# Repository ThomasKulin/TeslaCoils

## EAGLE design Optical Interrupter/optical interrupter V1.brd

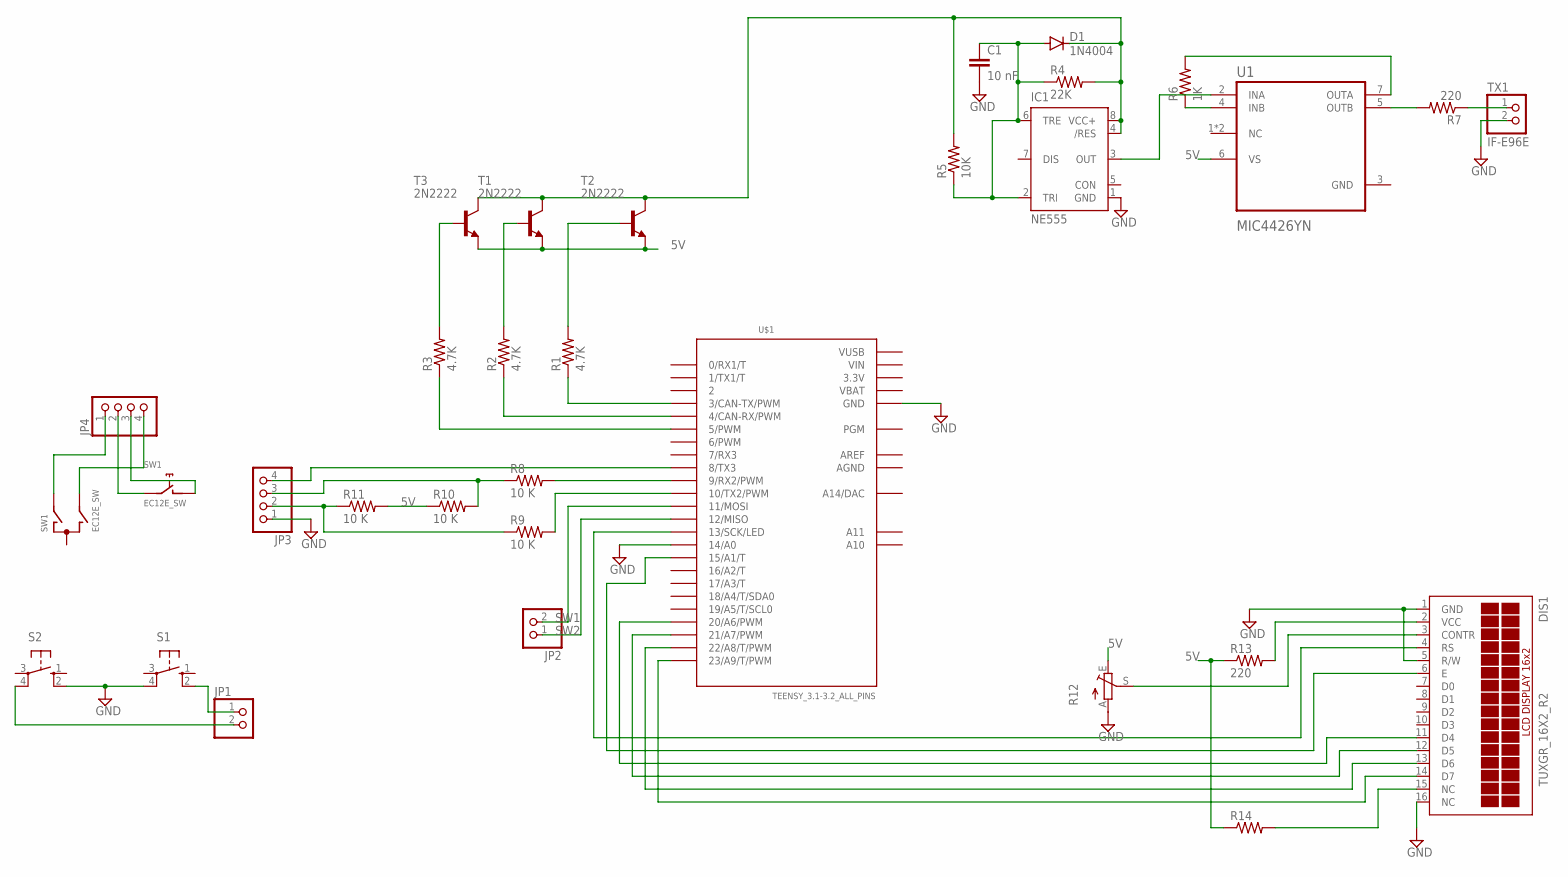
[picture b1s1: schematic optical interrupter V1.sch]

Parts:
C1: 10 nF; C050-024X044
D1: 1N4004; DO41-10
DIS1: TUXGR_16X2_R2
IC1: NE555; DIL-08
JP1, JP2: PINHD-1X2; 1X02
JP3, JP4: PINHD-1X4; 1X04
R1, R2, R3: 4.7K; 0207/7
R4: 22K; 0207/7
R5: 10K; 0207/7
R6: 1K; 0207/7
R7, R13: 220; 0207/7
R8, R9, R10, R11: 10 K; 0207/7
R12: TRIM_EU-B64W; B64W
R14: R-US_0207/7; 0207/7
S1, S2: 10-XX; B3F-10XX
SW1: EC12E_SW; ALPS_EC12E_SW
T1, T2, T3: 2N2222; TO92-EBC-OVAL
TX1: IF-E96E; 1X02
U1: MIC4426YN; DIP787W46P254L927H533Q8
U$1: TEENSY_3.1-3.2_ALL_PINS; TEENSY_3.0-3.2&LC_ALL_PINS

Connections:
3.3V: U$1.3.3V, U$1.3.3V1 (3.3V)
5V: R10.1, R11.2, R12.E, R13.1, R14.1, T1.E, T2.E, T3.E, U1.6 (VS)
AGND: U$1.AGND
AREF: U$1.AREF
GND: C1.2, DIS1.1 (GND), DIS1.5 (R/W), DIS1.16 (NC), IC1.1 (GND), JP3.1, R12.A, S1.4 (P1), S2.2 (S1), TX1.2, U1.3 (GND), U$1.14/A0, U$1.GND, U$1.GND1 (GND)
unnamed: R1.1, U$1.3 (3/CAN-TX/PWM)
unnamed: R2.1, U$1.4 (4/CAN-RX/PWM)
unnamed: R3.1, U$1.5 (5/PWM)
unnamed: R1.2, T2.B
unnamed: R3.2, T3.B
unnamed: R2.2, T1.B
unnamed: D1.C, IC1.4 (/RES), IC1.8 (VCC+), R4.2, R5.2, T1.C, T2.C, T3.C
unnamed: C1.1, D1.A, IC1.2 (TRI), IC1.6 (TRE), R4.1, R5.1
unnamed: IC1.3 (OUT), U1.2 (INA)
unnamed: R6.1, U1.4 (INB)
unnamed: R6.2, U1.7 (OUTA)
unnamed: R7.2, U1.5 (OUTB)
unnamed: R7.1, TX1.1
unnamed: JP4.2, SW1.E (2)
unnamed: JP4.4, SW1.B
unnamed: JP3.4, U$1.8 (8/TX3)
unnamed: R9.2, U$1.10 (10/TX2/PWM)
unnamed: R8.2, U$1.9 (9/RX2/PWM)
unnamed: JP3.3, R8.1, R10.2
unnamed: JP3.2, R9.1, R11.1
unnamed: DIS1.2 (VCC), R13.2
unnamed: DIS1.3 (CONTR), R12.S
unnamed: DIS1.4 (RS), U$1.13 (13/SCK/LED)
unnamed: DIS1.6 (E), U$1.15/A1 (15/A1/T)
unnamed: DIS1.11 (D4), U$1.20/A6 (20/A6/PWM)
unnamed: DIS1.12 (D5), U$1.21/A7 (21/A7/PWM)
unnamed: DIS1.13 (D6), U$1.22/A8 (22/A8/T/PWM)
unnamed: DIS1.14 (D7), U$1.23/A9 (23/A9/T/PWM)
unnamed: DIS1.15 (NC), R14.2
unnamed: JP4.1, SW1.A
unnamed: JP4.3, SW1.D (1)
unnamed: JP1.1, S1.2 (S1)
unnamed: JP1.2, S2.4 (P1)
SW1: JP2.2, U$1.11 (11/MOSI)
SW2: JP2.1, U$1.12 (12/MISO)
VBAT: U$1.VBAT
VIN: U$1.VIN
VUSB: U$1.VUSB

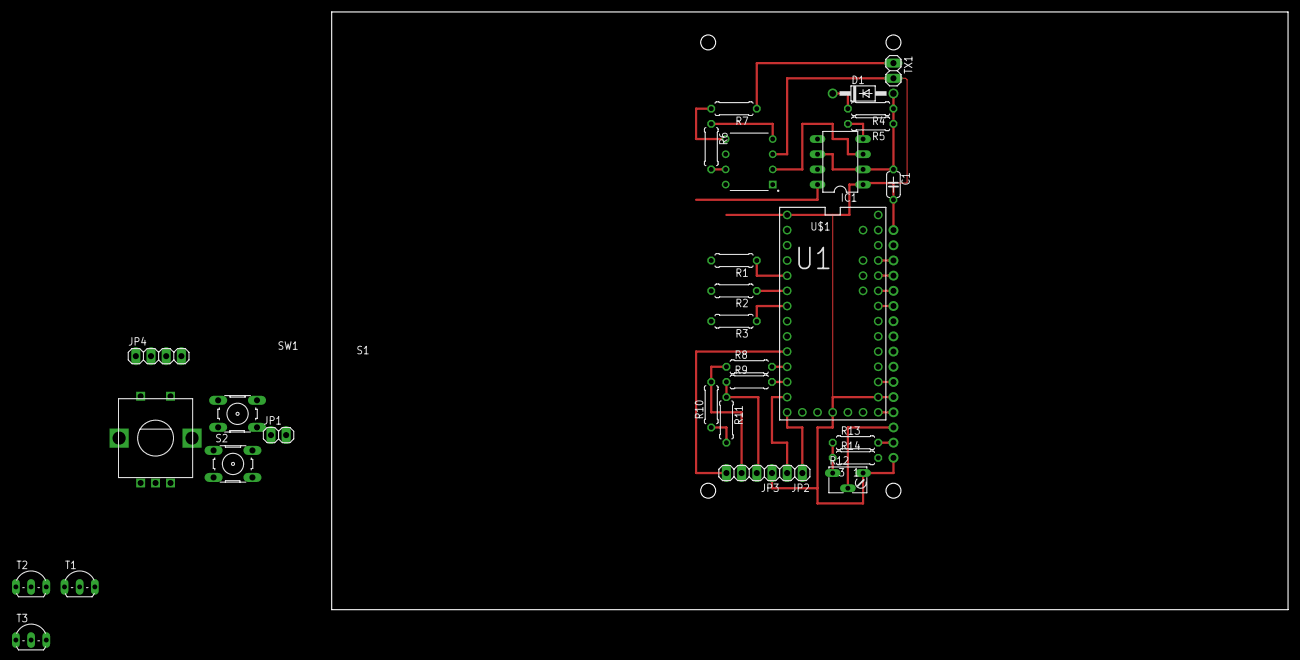
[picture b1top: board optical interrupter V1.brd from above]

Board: 2 copper layers, 160.0 x 100.0 mm, 31 parts (1 on the bottom side), 38 nets.

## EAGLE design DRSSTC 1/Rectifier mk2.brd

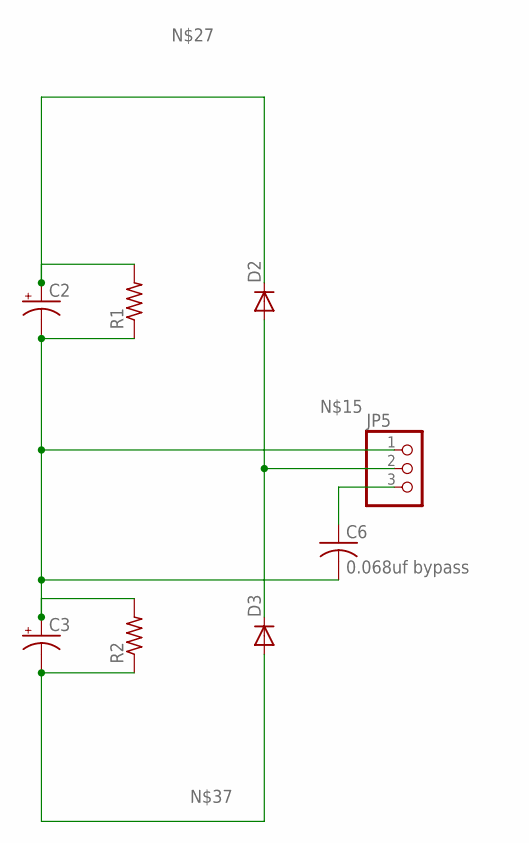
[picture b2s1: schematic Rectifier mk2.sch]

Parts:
C2, C3: CPOL-USE10-35; EB35D
C6: 0.068uf bypass; C150-084X183
D2, D3: DIODE-TO220V; TO220ACS
JP5: PINHD-1X3-9.5; 1X03-9.5
R1, R2: R-US_0207/10; 0207/10

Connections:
unnamed: C6.1, JP5.3
unnamed: C2.-, C3.+, C6.2, JP5.1, R1.1, R2.2
unnamed: D2.A, D3.C, JP5.2
unnamed: C2.+, D2.C, R1.2
unnamed: C3.-, D3.A, R2.1

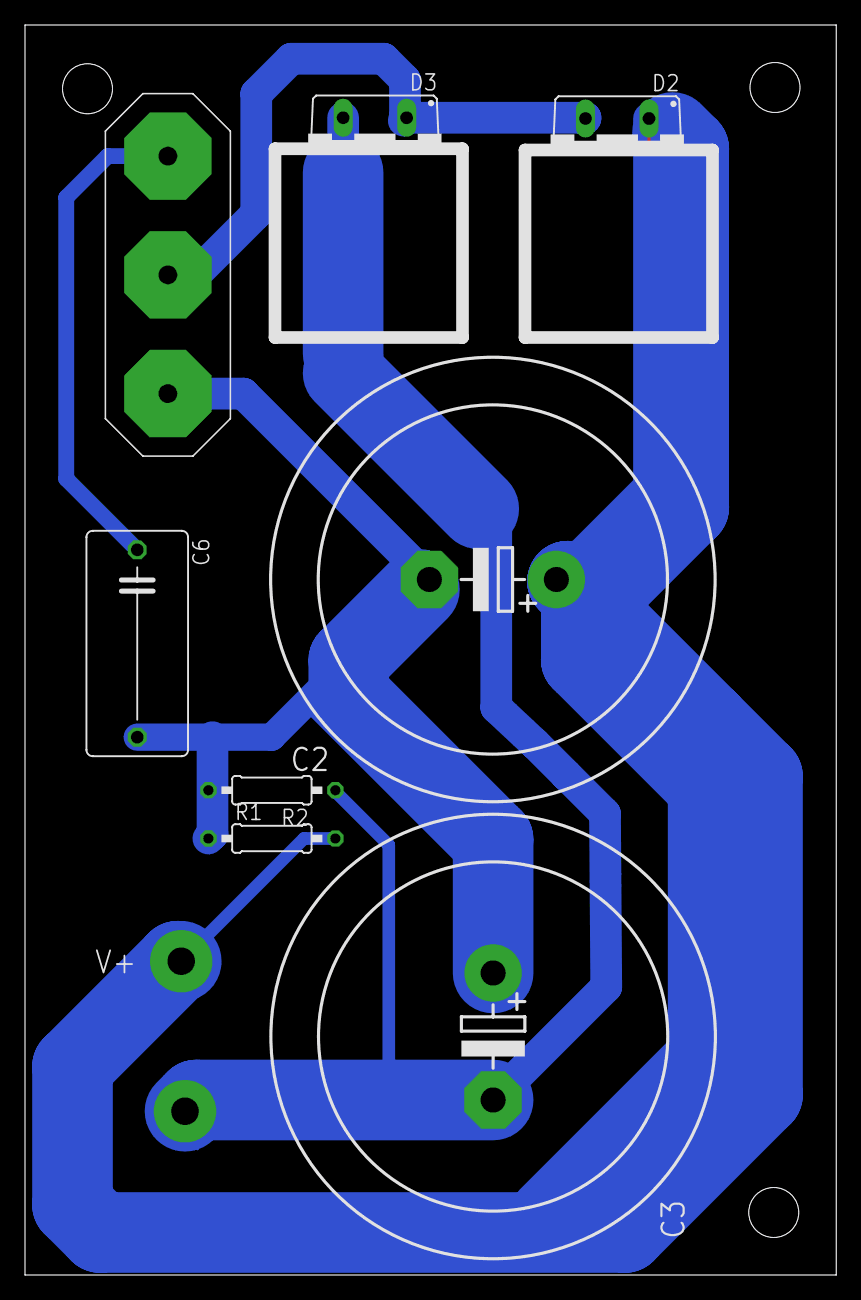
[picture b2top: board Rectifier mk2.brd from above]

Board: 2 copper layers, 64.9 x 100.0 mm, 8 parts (0 on the bottom side), 5 nets.

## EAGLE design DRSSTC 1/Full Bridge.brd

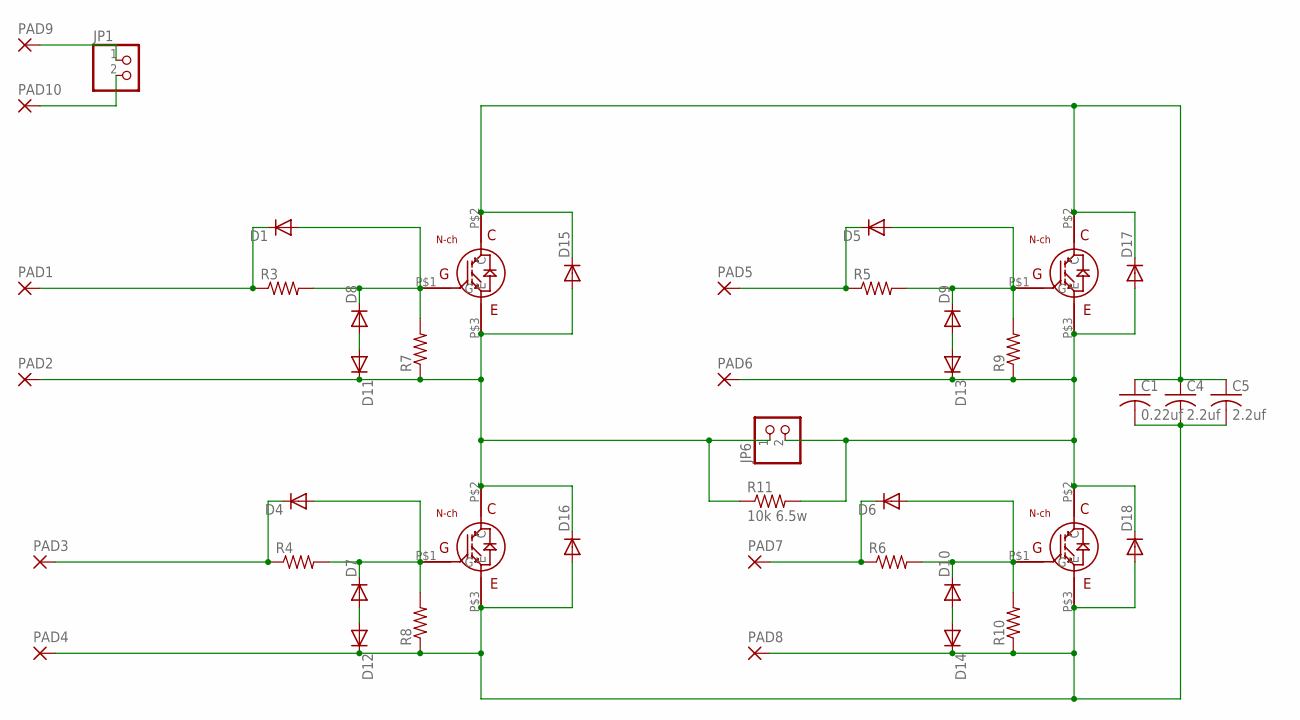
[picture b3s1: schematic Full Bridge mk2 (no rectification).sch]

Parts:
C1: 0.22uf; C375-155X418
C4, C5: 2.2uf; C275-134X316
D1, D4, D5, D6, D7, D8, D9, D10, D11, D12, D13, D14: DIODE-DO-214AC; DO-214AC
D15, D16, D17, D18: DIODE-DO201-15; DO201-15
JP1: PINHD-1X2; 1X02
JP6: PINHD-1X2-9.5; 1X02-9.5
PAD1, PAD2, PAD3, PAD4, PAD5, PAD6, PAD7, PAD8, PAD9, PAD10: SMD5; SMD2,54-5,08
R3, R4, R5, R6: R-US_0207/10; 0207/10
R7, R8, R9, R10: R-US_R0805; R0805
R11: 10k 6.5w; P0817/22
U$1, U$2, U$3, U$4: TO-247B; TO-247-FLATFIX

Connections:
unnamed: D1.A, D8.C, R3.2, R7.2, U$1.P$1 (G)
unnamed: JP1.1, PAD9.1
unnamed: JP1.2, PAD10.1
unnamed: D1.C, PAD1.1, R3.1
unnamed: D4.C, PAD3.1, R4.1
unnamed: D4.A, D7.C, R4.2, R8.2, U$2.P$1 (G)
unnamed: D5.A, D9.C, R5.2, R9.2, U$3.P$1 (G)
unnamed: D5.C, PAD5.1, R5.1
unnamed: D6.A, D10.C, R6.2, R10.2, U$4.P$1 (G)
unnamed: D6.C, PAD7.1, R6.1
unnamed 11: C1.1, C4.1, C5.1, D15.C, D17.C, U$1.P$2 (C), U$3.P$2 (C); also elsewhere on the board
unnamed: D7.A, D12.A
unnamed: D8.A, D11.A
unnamed: D11.C, D15.A, D16.C, JP6.1, PAD2.1, R7.1, R11.1, U$1.P$3 (E), U$2.P$2 (C)
unnamed: D13.C, D17.A, D18.C, JP6.2, PAD6.1, R9.1, R11.2, U$3.P$3 (E), U$4.P$2 (C)
unnamed 18: C1.2, C4.2, C5.2, D12.C, D14.C, D16.A, D18.A, PAD4.1, PAD8.1, R8.1, R10.1, U$2.P$3 (E), U$4.P$3 (E); also elsewhere on the board
unnamed: D10.A, D14.A
unnamed: D9.A, D13.A

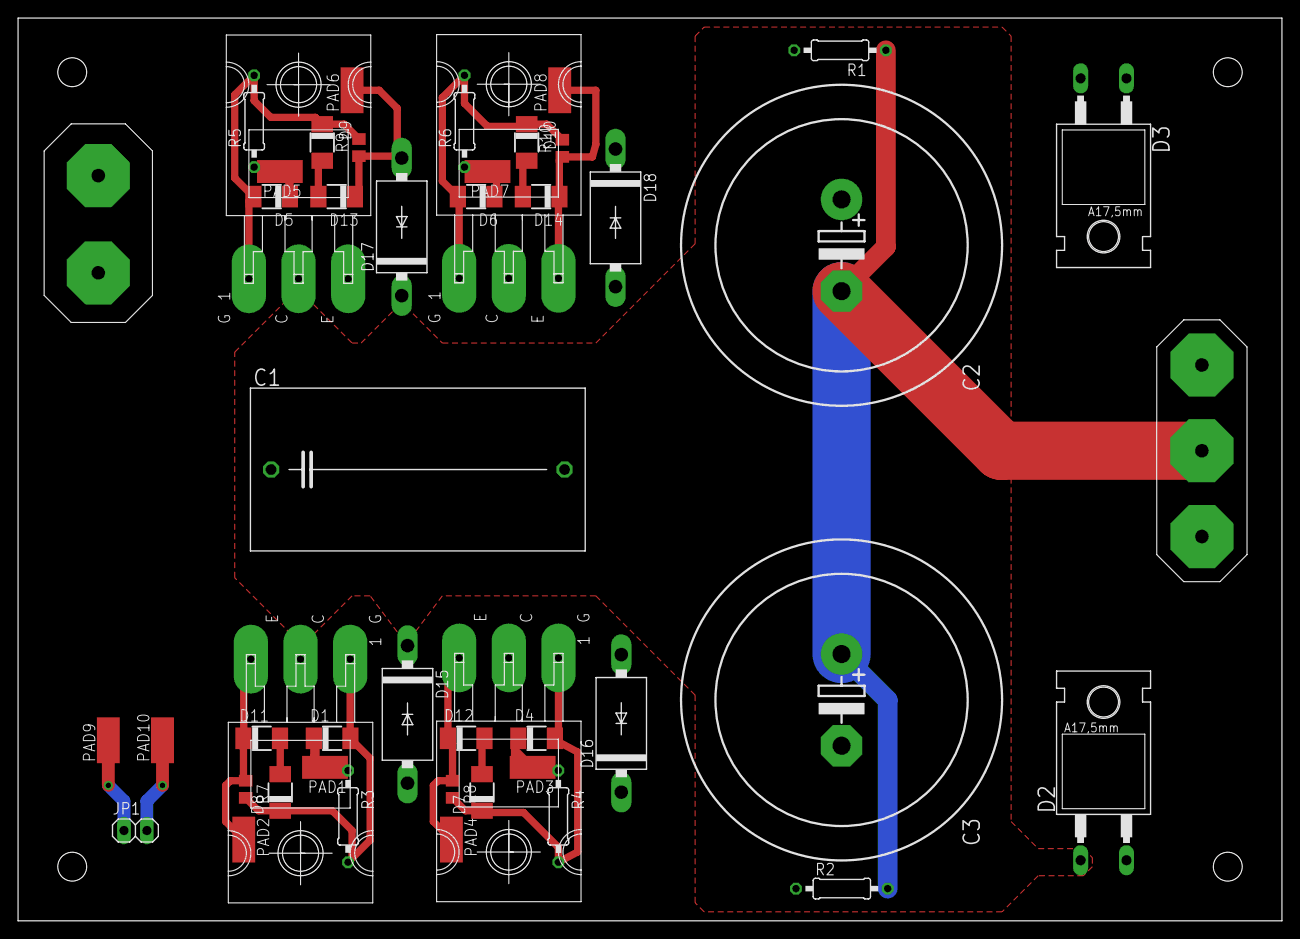
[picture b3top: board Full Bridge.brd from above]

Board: 2 copper layers, 140.0 x 100.0 mm, 48 parts (0 on the bottom side), 20 nets.

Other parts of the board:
C2, C3: EB35D
D2, D3: TO220AC
JP5: 1X03-9.5
R1, R2: 0207/10

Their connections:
unnamed 11: C2.+, D2.C, R1.2; also elsewhere on the board
unnamed: C2.-, C3.+, JP5.2, R1.1, R2.2
unnamed: D2.A, D3.C, JP5.1
unnamed 18: C3.-, D3.A, R2.1; also elsewhere on the board

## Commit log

2019-08-18 uploading existing progress. functional layouts with minor edits required.
2019-08-19 completed output stage of schematic. Input/output still incomplete
2019-08-20 partially completed breadboard layout
2019-08-20 completed board layout, maybe add a connector for the buttons / rotary encoder
2019-11-05 updated file structure
